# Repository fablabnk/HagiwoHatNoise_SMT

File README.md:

# HagiwoHatNoise SMT - first steps in PCBA

https://jlcpcb.com/parts/all-electronic-components

- we won't have pots, jacks or power header assembled, just resistors/caps/transistors/maybe LED
- it's better/less costly to place components just on one side of the board
- for v1.0 we continue to mount arduino on pin headers
- for v2.0 we can aim to just use atmega chip directly (though it likely won't be cheaper)
- it is possible to use BOM tool to autodetect parts, though its detection isn't great
	- it's a bit chicken and egg i.e. our BOM is through-hole parts and we need to know which SMT parts to use
- to save cash look for 'basic' parts, as extended parts incur a picking/loading fee
	- though not many fall into that category 
	- some resistors are classed as 'basic'
- some specifics for the Hagiwo hat circuit are:
-- you can use any common NPN type transistor, not just 2SC1815
-- Schottky diodes have low forward voltage drop (Vf) which provides earlier protection to the Arduino pins

- choose parts, download footprints

JLCPCB’s Online Tools: JLCPCB offers tools like the "SMT Parts Library" where you can select components and automatically download their corresponding footprints.

https://componentsearchengine.com/
https://github.com/uPesy/easyeda2kicad.py

There is a tick box for 'basic parts', and a github which lists them all:
https://github.com/josemariaaraujo/JLCPCB-Basic-Parts/blob/master/Basic%20Parts.csv

you preorder parts to reserve them before submitting a PCBA order

PCBA
- MLCCs, 50V
- you can search for all values at once, check package and manufacturer
- some have thumbs up symbol (no feeder fee)
2 x 100pF (101) ceramic capacitor
1 x 22nF (223) ceramic capacitor
1 x 3.3nF (332) ceramic capacitor
1 x 2.2uF (225) ceramic capacitor
1 x 100nF (104) ceramic capacitor
1 x 10uF electrolytic capacitor
6 x BAT43 diodes (Vf < 0.3V) rated at 10mV
1 x 2SC1815 transistor 
6 x 1K resistor
1 x 33K resistor
1 x 470 resistor
1 x 2.7K resistor
4 x 100K resistor

Self-Assembly
1 x LED
3 x 100K pots
4 x thonkiconns
1 x Eurorack_Power_16pin_Shrouded

PCBA requires compatible BOM and CPL files

There are two support articles for getting these from KiCad
https://jlcpcb.com/help/article/81-How-to-generate-the-BOM-and-Centroid-file-from-KiCAD
https://jlcpcb.com/help/article/66-How-to-Generate-BOM-and-Centroid-Files-from-KiCad-in-Linux

This plugin described in the 2nd article can help
https://github.com/fullyautomated/KiJLC
In eeschema must choose Tools -> Generate Legacy Bill of Materials

AttributeError: `BOARD` object has no attribute `GetModules`
https://github.com/fullyautomated/KiJLC/issues/3

Also:
https://gist.github.com/arturo182/a8c4a4b96907cfccf616a1edb59d0389

This one seems best/most up to date:
https://github.com/Bouni/kicad-jlcpcb-tools

There’s another one which is in the PCM by bennymeg which would be more straightforward to install, search in the PCM.

https://pretalx.kicad.org/kicon-europe-2024/cfp

https://github.com/kweiwen/benjolin/tree/master

# Part Picks

Foshan Blue Rocket Elec 2SC1815M-GR C305425
50V 300mW 200@2mA,6V 150mA NPN SOT-23 Bipolar Transistors - BJT ROHS
SOT-23

TOSHIBA CUS10S30,H3F C146335
30V 230mV@100mA 1A SC-76(SOD-323) Schottky Barrier Diodes (SBD) ROHS
SC-76(SOD-323)

Capxon International Elec HV100M050C055ETR C402532
10uF 50V ±20% SMD,D5xL5.5mm Aluminum Electrolytic Capacitors - SMD ROHS
SMD,D5xL5.5mm

CCTC TCC1206X7R225K500HT C2903669
50V 2.2uF X7R ±10% 1206 Multilayer Ceramic Capacitors MLCC - SMD/SMT ROHS
1206

HRE CGA0402X7R104K500GT C6119785
50V 100nF X7R ±10% 0402 Multilayer Ceramic Capacitors MLCC - SMD/SMT ROHS
0402

Walsin Tech Corp 0402B332J500CT C237209
50V 3.3nF X7R ±5% 0402 Multilayer Ceramic Capacitors MLCC - SMD/SMT ROHS
0402

Darfon Elec C0603NP0101JGT C258474
50V 100pF NP0 ±5% 0201 Multilayer Ceramic Capacitors MLCC - SMD/SMT ROHS
0201

HUI JU NL0805B223K500CPBN C969994
50V 22nF ±10% 0805 Multilayer Ceramic Capacitors MLCC - SMD/SMT ROHS
0805

UNI-ROYAL(Uniroyal Elec) AS0606J0272T5E C966063
600mW Thick Film Resistors 200V ±100ppm/℃ ±5% 2.7kΩ 1206 Chip Resistor - Surface Mount ROHS
1206

UNI-ROYAL(Uniroyal Elec) HP05W3J0333T5E C2774724
333.333mW Thick Film Resistors 150V ±100ppm/℃ ±5% 33kΩ 0805 Chip Resistor - Surface Mount ROHS
0805

UNI-ROYAL(Uniroyal Elec) CQ05W8J0102T5E C966525
125mW 150V ±100ppm/℃ ±5% 1kΩ 0805 Chip Resistor - Surface Mount ROHS
0805

UNI-ROYAL(Uniroyal Elec) NQ06W4F1003T5E C965069
250mW 200V ±100ppm/℃ ±1% 100kΩ 1206 Chip Resistor - Surface Mount ROHS
1206

Ever Ohms Tech CR0402F470RQ10Z C881342
63mW Thick Film Resistors ±100ppm/℃ ±1% 470Ω 0402 Chip Resistor - Surface
0402

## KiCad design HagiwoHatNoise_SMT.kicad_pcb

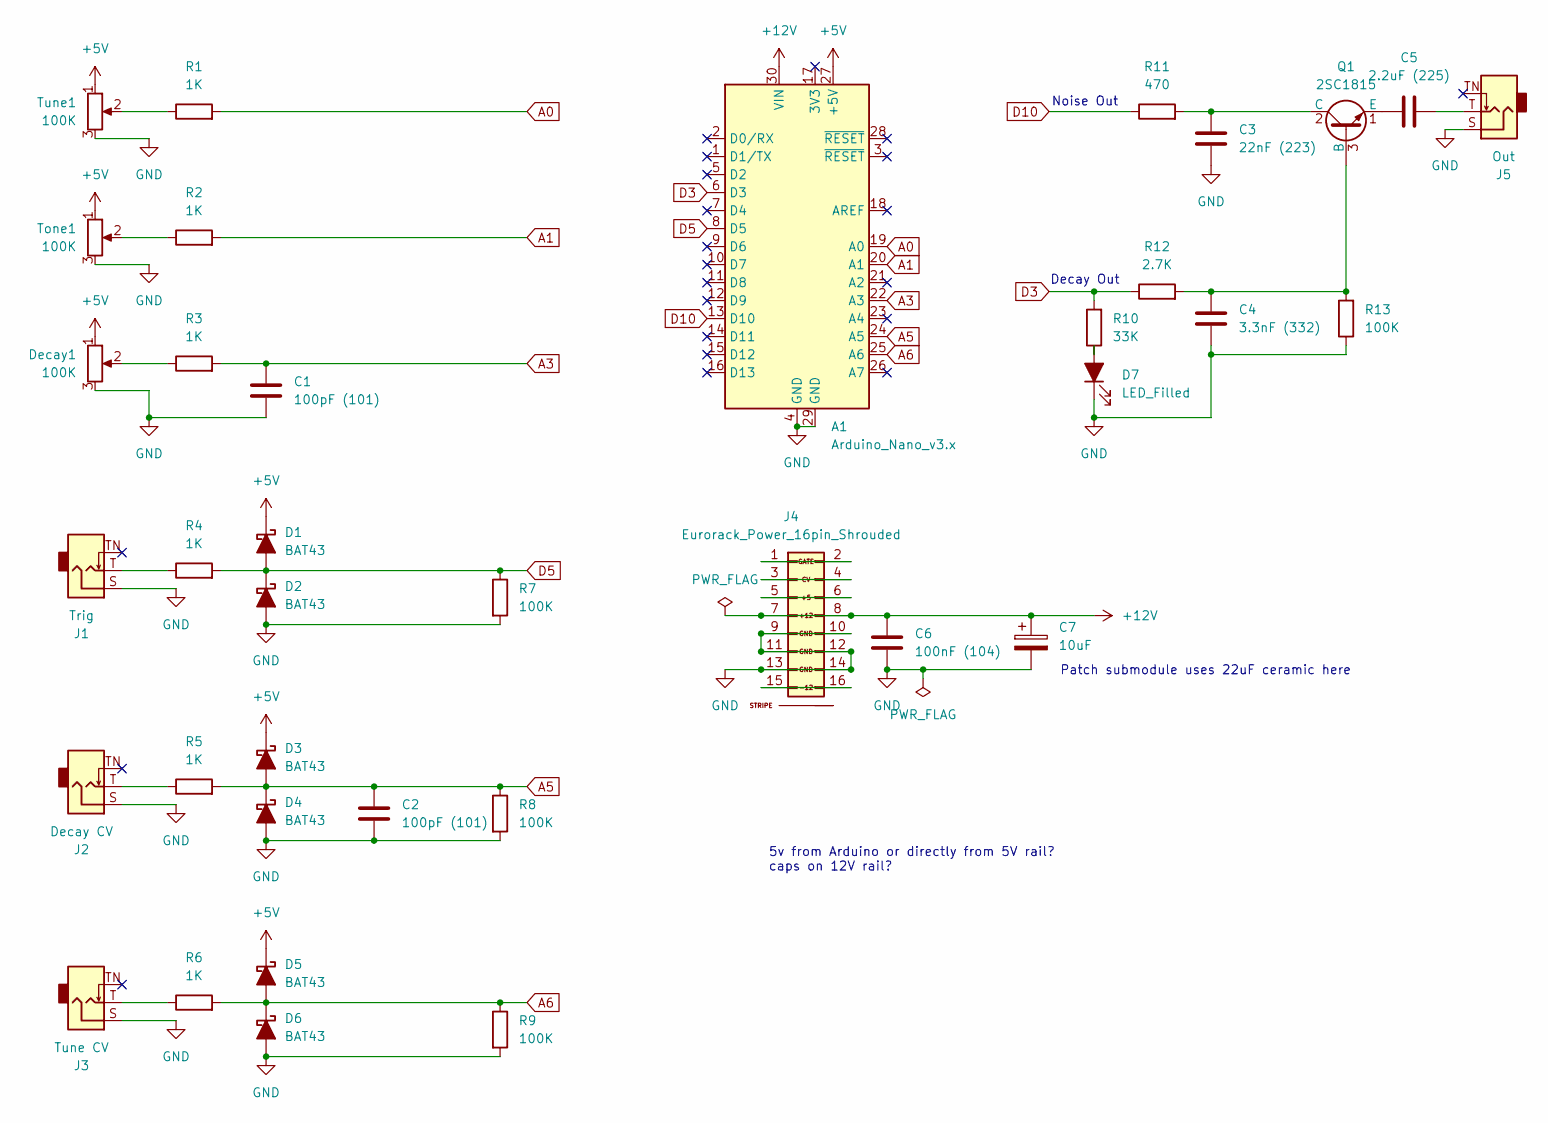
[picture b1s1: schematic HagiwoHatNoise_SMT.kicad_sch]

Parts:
A1: Arduino_Nano_v3.x; Arduino_Nano
C1, C2: 100pF (101); C_0201_0603Metric
C3: 22nF (223); C_0805_2012Metric
C4: 3.3nF (332); C_0402_1005Metric
C5: 2.2uF (225); C_1206_3216Metric
C6: 100nF (104); C_0402_1005Metric
C7: 10uF; CP_Elec_5x5.4
D1, D2, D3, D4, D5, D6: BAT43; D_SOD-323
D7: LED_Filled; LED_D5.0mm
Decay1: 100K; Pot_9mm_DShaft_RemovedPins4_5
J1: Trig; EighthInch_PJ398SM_T_TN_S
J2: Decay CV; EighthInch_PJ398SM_T_TN_S
J3: Tune CV; EighthInch_PJ398SM_T_TN_S
J4: Eurorack_Power_16pin_Shrouded; Pins_2x08_2.54mm_TH_EuroPower_Shrouded_Minimal; Part Number LL1007-1 (2*8 HITEMP)
J5: Out; EighthInch_PJ398SM_T_TN_S
Q1: 2SC1815; SOT-23
R1, R2, R3, R4, R5, R6: 1K; R_0805_2012Metric
R7, R8, R9, R13: 100K; R_1206_3216Metric
R10: 33K; R_0805_2012Metric
R11: 470; R_0402_1005Metric
R12: 2.7K; R_1206_3216Metric
Tone1: 100K; Pot_9mm_DShaft_RemovedPins4_5
Tune1: 100K; Pot_9mm_DShaft_RemovedPins4_5

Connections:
+5V: A1.27 (+5V), D1.1 (K), D3.1 (K), D5.1 (K), Decay1.1, Tone1.1, Tune1.1
+12V: A1.30 (VIN), C6.1, C7.1, J4.7 (12V), J4.8 (+12V)
A0: A1.19 (A0), R1.2
A1: A1.20 (A1), R2.2
A3: A1.22 (A3), C1.1, R3.2
A5: A1.24 (A5), C2.1, D3.2 (A), D4.1 (K), R5.2, R8.1
A6: A1.25 (A6), D5.2 (A), D6.1 (K), R6.2, R9.1
D3: A1.6 (D3), R10.2, R12.1
D5: A1.8 (D5), D1.2 (A), D2.1 (K), R4.2, R7.1
D10: A1.13 (D10), R11.1
GND: A1.4 (GND), A1.29 (GND), C1.2, C2.2, C3.2, C4.2, C6.2, C7.2, D2.2 (A), D4.2 (A), D6.2 (A), D7.1 (K), Decay1.3, J1.S, J2.S, J3.S, J4.9 (GND), J4.10 (GND), J4.11 (GND), J4.12 (GND), J4.13 (-12), J4.14 (-12V), J5.S, R7.2, R8.2, R9.2, R13.1, Tone1.3, Tune1.3
unnamed: C5.2, J5.T
unnamed: D7.2 (A), R10.1
unnamed: Decay1.2, R3.1
unnamed: J1.T, R4.1
unnamed: J2.T, R5.1
unnamed: J3.T, R6.1
unnamed: J4.1, J4.2
unnamed: J4.3, J4.4
unnamed: J4.5 (+12V), J4.6
unnamed: J4.15 (-12V), J4.16
unnamed: C4.1, Q1.3 (B), R12.2, R13.2
unnamed: C3.1, Q1.2 (C), R11.2
unnamed: C5.1, Q1.1 (E)
unnamed: R1.1, Tune1.2
unnamed: R2.1, Tone1.2

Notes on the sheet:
5v from Arduino or directly from 5V rail? caps on 12V rail?
Noise Out
Patch submodule uses 22uF ceramic here
Decay Out

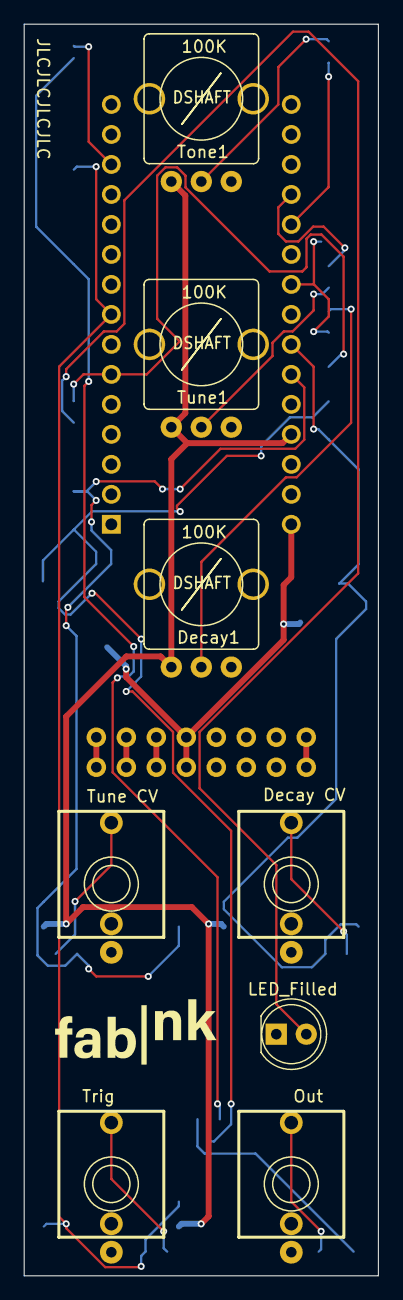
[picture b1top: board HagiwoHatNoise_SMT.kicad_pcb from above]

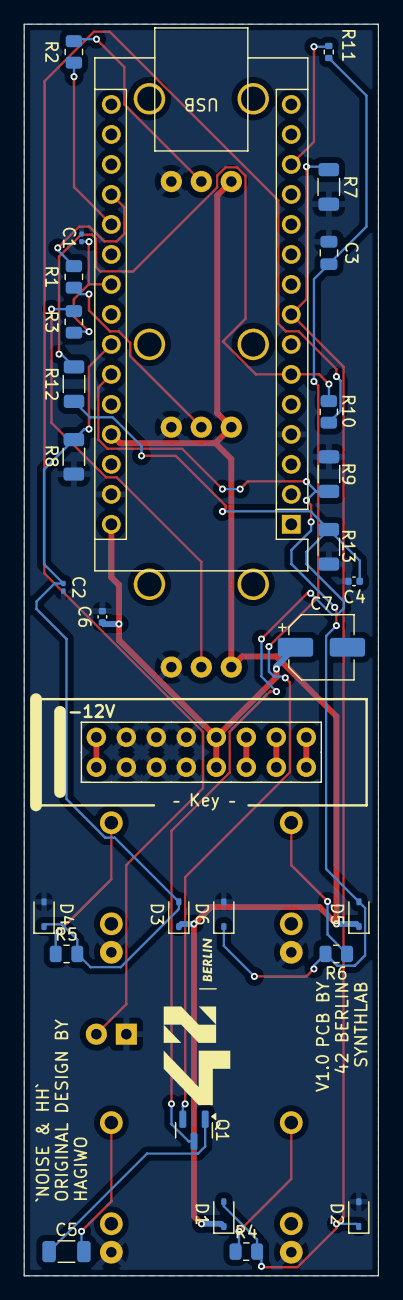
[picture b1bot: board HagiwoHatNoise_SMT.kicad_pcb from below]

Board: 2 copper layers, 30.0 x 106.0 mm, 37 parts (29 on the bottom side), 26 nets.

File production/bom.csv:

Designator,Footprint,Quantity,Value,LCSC Part #
A1,Arduino_Nano,1,Arduino_Nano_v3.x,
"C1, C2",0201,2,100pF (101),
C3,0805,1,22nF (223),
C4,0402,1,3.3nF (332),
C5,1206,1,2.2uF (225),
C6,0402,1,100nF (104),
C7,CP_Elec_5x5.4,1,10uF,
"D1, D2, D3, D4, D5, D6",D_SOD-323,6,BAT43,
D7,LED_D5.0mm,1,LED_Filled,
"Decay1, Tone1, Tune1",Pot_9mm_DShaft_RemovedPins4_5,3,100K,
J1,EighthInch_PJ398SM_T_TN_S,1,Trig,
J2,EighthInch_PJ398SM_T_TN_S,1,Decay CV,
J3,EighthInch_PJ398SM_T_TN_S,1,Tune CV,
J4,Pins_2x08_2.54mm_TH_EuroPower_Shrouded_Minimal,1,Eurorack_Power_16pin_Shrouded,
J5,EighthInch_PJ398SM_T_TN_S,1,Out,
Q1,SOT-23,1,2SC1815,
"R1, R2, R3, R4, R5, R6",0805,6,1K,
R10,0805,1,33K,
R11,0402,1,470,
R12,1206,1,2.7K,
"R13, R7, R8, R9",1206,4,100K,
